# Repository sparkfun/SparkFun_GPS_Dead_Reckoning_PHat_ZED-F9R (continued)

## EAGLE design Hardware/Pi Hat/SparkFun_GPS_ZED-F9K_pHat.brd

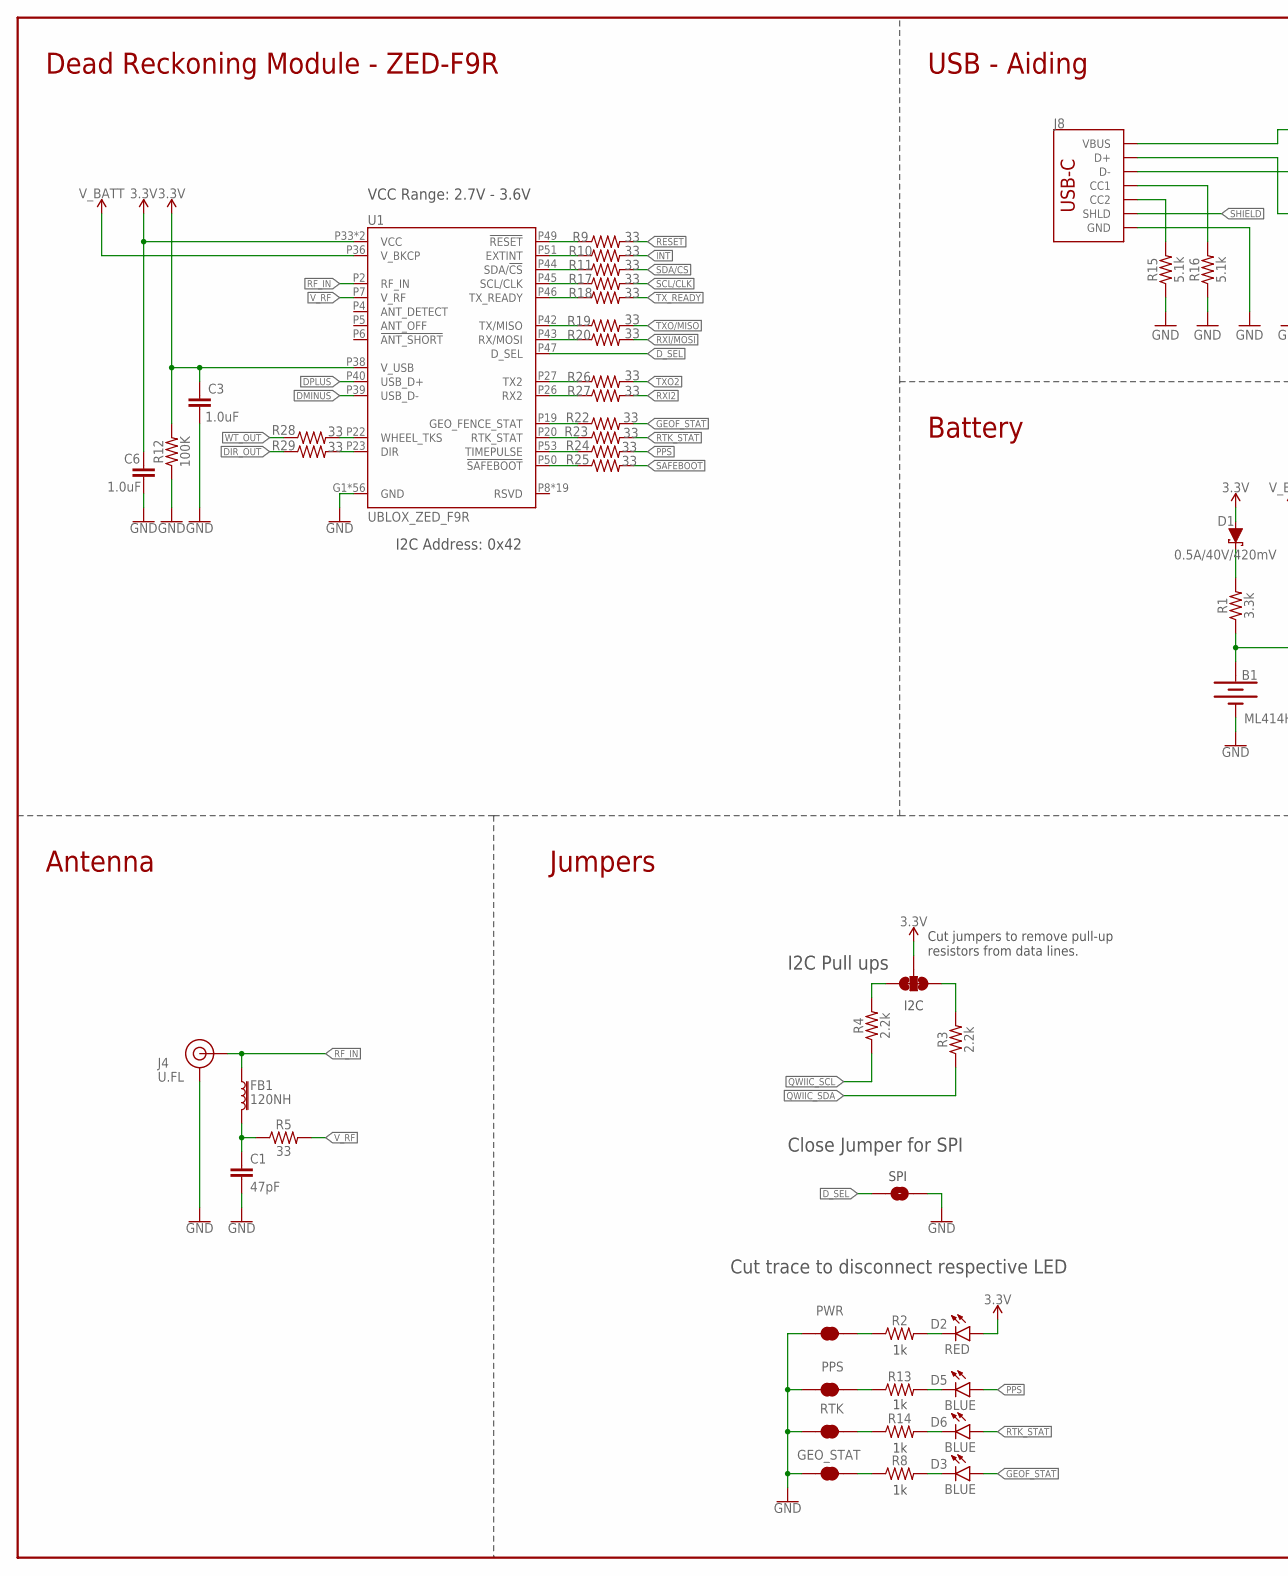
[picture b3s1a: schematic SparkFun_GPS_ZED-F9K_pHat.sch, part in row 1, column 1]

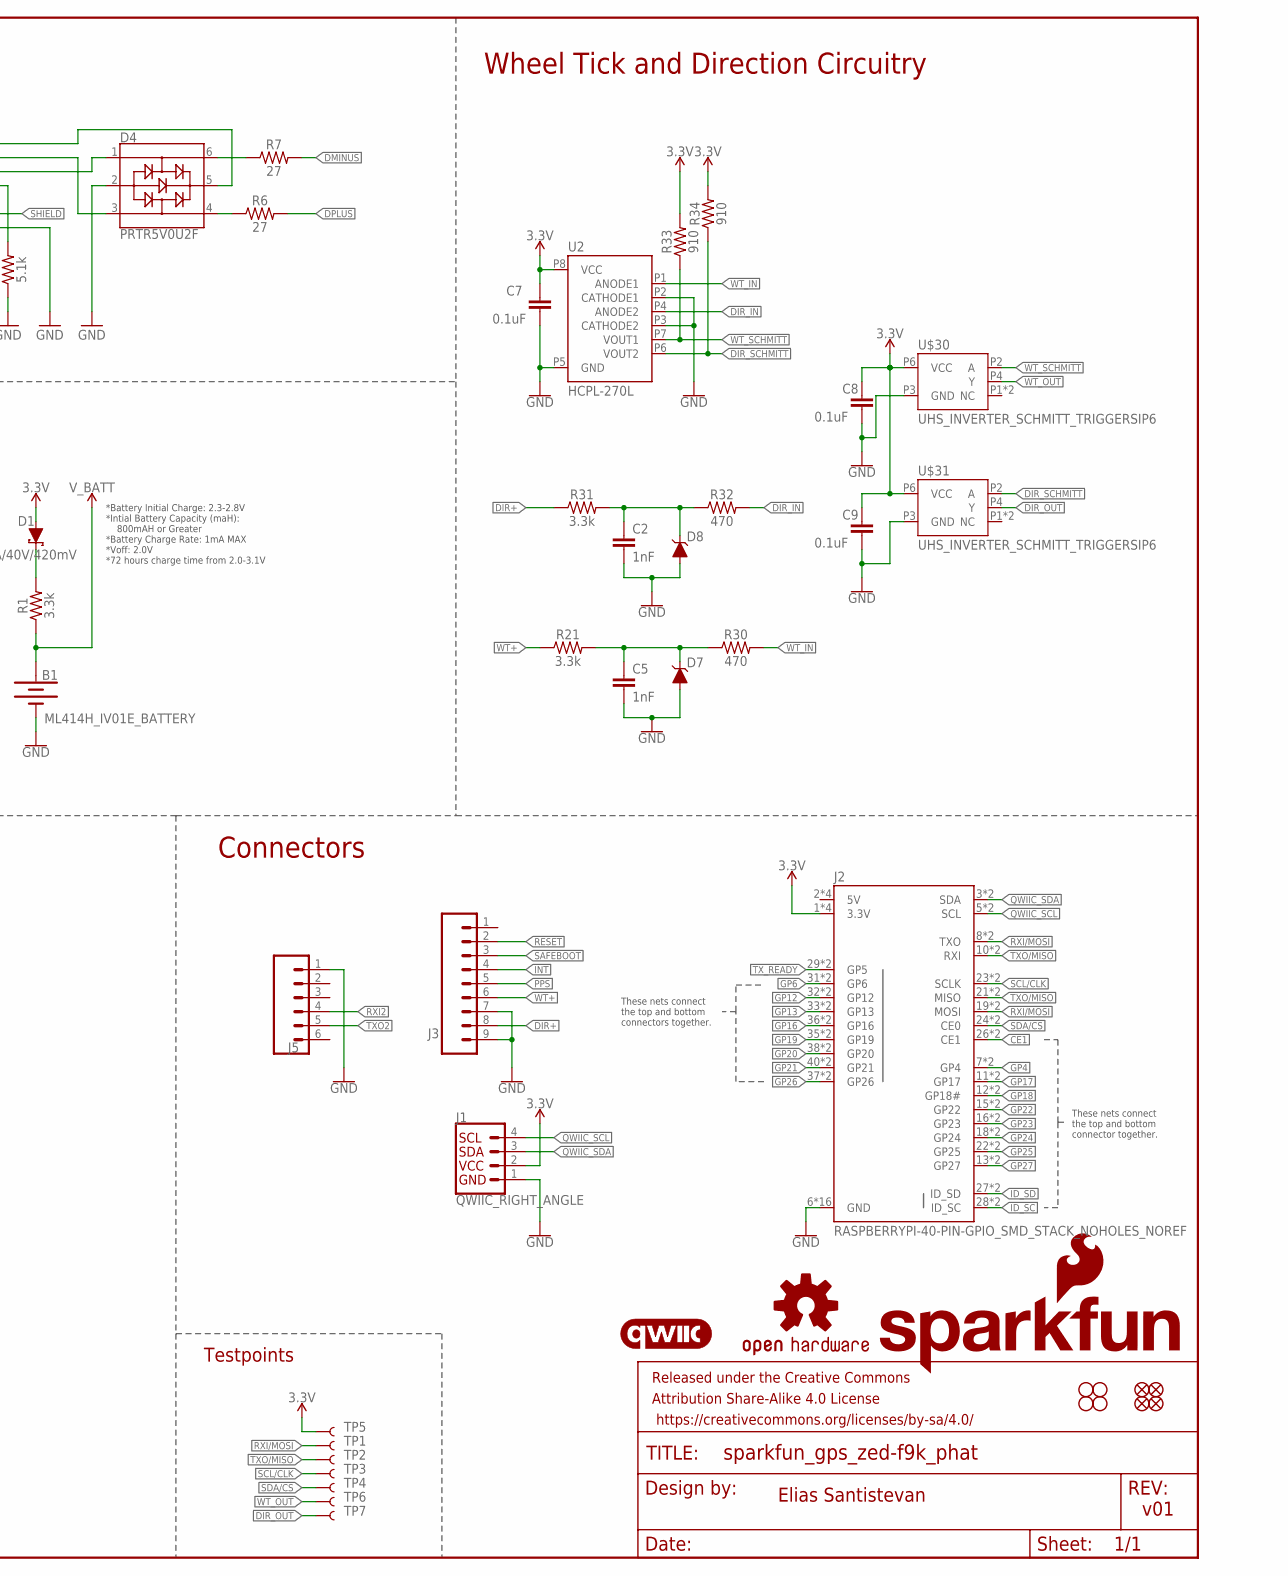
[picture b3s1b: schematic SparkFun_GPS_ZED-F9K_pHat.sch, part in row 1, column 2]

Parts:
B1: ML414H_IV01E_BATTERY; ML414H_IV01E
C1: 47pF; 0402
C2, C5: 1nF; 0402
C3, C6: 1.0uF; 0402
C7, C8, C9: 0.1uF; 0402
D1: 0.5A/40V/420mV; SOD-323
D2: RED; LED-0603
D3, D5, D6: BLUE; LED-0603
D4: PRTR5V0U2F; SOT886
D7, D8: 0.5A/40V/420mV; SOT23_BZX
FB1: 120NH; 0402_MURATA
FD9, FD10, FD11, FD12: FIDUCIALUFIDUCIAL; FIDUCIAL-MICRO
FRAME2: FRAME-LEDGER; CREATIVE_COMMONS
GEO_STAT: JUMPER-SMT_2_NC_TRACE_SILK; SMT-JUMPER_2_NC_TRACE_SILK
H9, H10, H11, H12: STAND-OFFTIGHT; STAND-OFF-TIGHT
J1: QWIIC_RIGHT_ANGLE; JST04_1MM_RA
J2: RASPBERRYPI-40-PIN-GPIO_SMD_STACK_NOHOLES_NOREF; RASPBERRY_PI_HAT_40_PIN_SMD_STACKABLE_NOHOLES_NOREF
J3: CONN_09NO_SILK; 1X09_NO_SILK
J4: U.FL
J5: CONN_06NO_SILK_NO_POP; 1X06_NO_SILK
J8: USB_C_2-LAYER; USB-C-16P
JP1: JUMPER-SMT_2_NO_SILK; SMT-JUMPER_2_NO_SILK
JP2: JUMPER-SMT_3_2-NC_TRACE_SILK; SMT-JUMPER_3_2-NC_TRACE_SILK
LOGO1: SFE_LOGO_NAME_FLAME.2_INCH; SFE_LOGO_NAME_FLAME_.2
LOGO2: OSHW-LOGOM; OSHW-LOGO-M
LOGO3: QWIIC_LOGO_5MM; QWIIC_5MM
PPS: JUMPER-SMT_2_NC_TRACE_SILK; SMT-JUMPER_2_NC_TRACE_SILK
PWR: JUMPER-SMT_2_NC_TRACE_SILK; SMT-JUMPER_2_NC_TRACE_SILK
R1, R21, R31: 3.3k; 0603
R2, R8, R13, R14: 1k; 0603
R3, R4: 2.2k; 0603
R5, R9, R10, R11, R17, R18, R19, R20, R22, R23, R24, R25, R26, R27, R28, R29: 33; 0603
R6, R7: 27; 0603
R12: 100K; 0402
R15, R16: 5.1k; 0402
R30, R32: 470; 0603
R33, R34: 910; 0603
RTK: JUMPER-SMT_2_NC_TRACE_SILK; SMT-JUMPER_2_NC_TRACE_SILK
TP1, TP2, TP3, TP4, TP5, TP6, TP7: TEST-POINT3X4; PAD.03X.04
U1: UBLOX_ZED_F9R
U2: HCPL-270L; SOP_8-PIN
U$30, U$31: UHS_INVERTER_SCHMITT_TRIGGERSIP6; SIP6

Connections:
3.3V: C3.1, C6.1, C7.1, C8.1, C9.1, D1.A, D2.A, J1.2, J2.1 (3.3V), J2.1B (3.3V), J2.17 (3.3V), J2.17B (3.3V), JP2.2, R12.2, R33.2, R34.2, TP5.P$1, U1.P33 (VCC), U1.P34 (VCC), U1.P38 (V_USB), U2.P8 (VCC), U$30.P6 (VCC), U$31.P6 (VCC)
5V: J2.2 (5V), J2.2B (5V), J2.4 (5V), J2.4B (5V)
!RESET: J3.2, R9.2
!SAFEBOOT: J3.3, R25.2
CE1: J2.26 (CE1), J2.26B (CE1)
DIR+: J3.8, R31.1
DIR_IN: R32.2, U2.P4 (ANODE2)
DIR_OUT: R29.1, TP7.P$1, U$31.P4 (Y)
DIR_SCHMITT: R34.1, U2.P6 (VOUT2), U$31.P2 (A)
DMINUS: R7.2, U1.P39 (USB_D-)
DPLUS: R6.2, U1.P40 (USB_D+)
D_SEL: JP1.1, U1.P47 (D_SEL)
GEOF_STAT: D3.A, R22.2
GND: B1.-, C1.2, C2.2, C3.2, C5.2, C6.2, C7.2, C8.2, C9.2, D4.2, D7.P1 (A), D8.P1 (A), GEO_STAT.1, J1.1, J2.6 (GND), J2.6B (GND), J2.9 (GND), J2.9B (GND), J2.14 (GND), J2.14B (GND), J2.20 (GND), J2.20B (GND), J2.25 (GND), J2.25B (GND), J2.30 (GND), J2.30B (GND), J2.34 (GND), J2.34B (GND), J2.39 (GND), J2.39B (GND), J3.7, J3.9, J4.1 (GND), J4.2 (GND), J5.1, J8.GND, J8.GND2 (GND), JP1.2, PPS.1, PWR.1, R12.1, R15.1, R16.1, RTK.1, U1.G1 (GND), U1.G2 (GND), U1.G3 (GND), U1.G4 (GND), U1.G5 (GND), U1.G6 (GND), U1.G7 (GND), U1.G8 (GND), U1.G9 (GND), U1.G10 (GND), U1.G11 (GND), U1.G12 (GND), U1.G13 (GND), U1.G14 (GND), U1.G15 (GND), U1.G16 (GND), U1.G17 (GND), U1.G18 (GND), U1.G19 (GND), U1.G20 (GND), U1.G21 (GND), U1.G22 (GND), U1.G23 (GND), U1.G24 (GND), U1.G25 (GND), U1.G26 (GND), U1.G27 (GND), U1.G28 (GND), U1.G29 (GND), U1.G30 (GND), U1.G31 (GND), U1.G32 (GND), U1.G33 (GND), U1.G34 (GND), U1.G35 (GND), U1.G36 (GND), U1.G37 (GND), U1.G38 (GND), U1.G39 (GND), U1.G40 (GND), U1.G41 (GND), U1.G42 (GND), U1.G43 (GND), U1.G44 (GND), U1.G45 (GND), U1.G46 (GND), U1.G47 (GND), U1.G48 (GND), U1.P1 (GND), U1.P3 (GND), U1.P12 (GND), U1.P14 (GND), U1.P32 (GND), U1.P37 (GND), U1.P41 (GND), U1.P48 (GND), U2.P2 (CATHODE1), U2.P3 (CATHODE2), U2.P5 (GND), U$30.P3 (GND), U$31.P3 (GND)
GP4: J2.7 (GP4), J2.7B (GP4)
GP6: J2.31 (GP6), J2.31B (GP6)
GP12: J2.32 (GP12), J2.32B (GP12)
GP13: J2.33 (GP13), J2.33B (GP13)
GP16: J2.36 (GP16), J2.36B (GP16)
GP17: J2.11 (GP17), J2.11B (GP17)
GP18: J2.12 (GP18#), J2.12B (GP18#)
GP19: J2.35 (GP19), J2.35B (GP19)
GP20: J2.38 (GP20), J2.38B (GP20)
GP21: J2.40 (GP21), J2.40B (GP21)
GP22: J2.15 (GP22), J2.15B (GP22)
GP23: J2.16 (GP23), J2.16B (GP23)
GP24: J2.18 (GP24), J2.18B (GP24)
GP25: J2.22 (GP25), J2.22B (GP25)
GP26: J2.37 (GP26), J2.37B (GP26)
GP27: J2.13 (GP27), J2.13B (GP27)
ID_SC: J2.28 (ID_SC), J2.28B (ID_SC)
ID_SD: J2.27 (ID_SD), J2.27B (ID_SD)
INT: J3.4, R10.2
unnamed: JP2.1, R3.2
unnamed: D1.C, R1.2
unnamed: JP2.3, R4.2
unnamed: D2.C, R2.2
unnamed: C1.1, FB1.P2 (2), R5.1
unnamed: D4.6, R7.1
unnamed: D4.4, R6.1
unnamed: PWR.2, R2.1
unnamed: D4.3, J8.A6 (D+), J8.B6 (D+)
unnamed: D4.5, J8.VBUS1 (VBUS), J8.VBUS2 (VBUS)
unnamed: D4.1, J8.A7 (D-), J8.B7 (D-)
unnamed: J8.B5 (CC2), R15.2
unnamed: R9.1, U1.P49 (!RESET!)
unnamed: R10.1, U1.P51 (EXTINT)
unnamed: R11.1, U1.P44 (SDA/!CS!)
unnamed: GEO_STAT.2, R8.1
unnamed: D3.C, R8.2
unnamed: J8.A5 (CC1), R16.2
unnamed: R17.1, U1.P45 (SCL/CLK)
unnamed: R18.1, U1.P46 (TX_READY)
unnamed: R19.1, U1.P42 (TX/MISO)
unnamed: R14.1, RTK.2
unnamed: PPS.2, R13.1
unnamed: D5.C, R13.2
unnamed: D6.C, R14.2
unnamed: R20.1, U1.P43 (RX/MOSI)
unnamed: C5.1, D7.P3 (C), R21.2, R30.1
unnamed: R22.1, U1.P19 (GEO_FENCE_STAT)
unnamed: R23.1, U1.P20 (RTK_STAT)
unnamed: R24.1, U1.P53 (TIMEPULSE)
unnamed: R25.1, U1.P50 (!SAFEBOOT!)
unnamed: R26.1, U1.P27 (TX2)
unnamed: R27.1, U1.P26 (RX2)
unnamed: R28.2, U1.P22 (WHEEL_TKS)
unnamed: R29.2, U1.P23 (DIR)
unnamed: C2.1, D8.P3 (C), R31.2, R32.1
PPS: D5.A, J3.5, R24.2
QWIIC_SCL: J1.4, J2.5 (SCL), J2.5B (SCL), R4.1
QWIIC_SDA: J1.3, J2.3 (SDA), J2.3B (SDA), R3.1
RF_IN: FB1.P1 (1), J4.FEED (SIGNAL), U1.P2 (RF_IN)
RTK_STAT: D6.A, R23.2
RXI2: J5.4, R27.2
RXI/MOSI: J2.8 (TXO), J2.8B (TXO), J2.19 (MOSI), J2.19B (MOSI), R20.2, TP1.P$1
SCL/CLK: J2.23 (SCLK), J2.23B (SCLK), R17.2, TP3.P$1
SDA/!CS: J2.24 (CE0), J2.24B (CE0), R11.2, TP4.P$1
SHIELD: J8.SHLD1 (SHLD), J8.SHLD2 (SHLD), J8.SHLD3 (SHLD), J8.SHLD4 (SHLD), J8.SHLD5 (SHLD), J8.SHLD6 (SHLD), J8.SHLD7 (SHLD), J8.SHLD8 (SHLD)
TXO2: J5.5, R26.2
TXO/MISO: J2.10 (RXI), J2.10B (RXI), J2.21 (MISO), J2.21B (MISO), R19.2, TP2.P$1
TX_READY: J2.29 (GP5), J2.29B (GP5), R18.2
V_BATT: B1.+, R1.1, U1.P36 (V_BKCP)
V_RF: R5.2, U1.P7 (V_RF)
WT+: J3.6, R21.1
WT_IN: R30.2, U2.P1 (ANODE1)
WT_OUT: R28.1, TP6.P$1, U$30.P4 (Y)
WT_SCHMITT: R33.1, U2.P7 (VOUT1), U$30.P2 (A)

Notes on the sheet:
v01
Elias Santistevan
Dead Reckoning Module - ZED-F9R
Battery
Connectors
Jumpers
Close Jumper for SPI
I2C Pull ups
Cut trace to disconnect respective LED
Antenna
*Battery Initial Charge: 2.3-2.8V *Intial Battery Capacity (maH): 800mAH or Greater *Battery Charge Rate: 1mA MAX *Voff: 2.0V *72 hours charge time from 2.0-3.1V
VCC Range: 2.7V - 3.6V
I2C Address: 0x42
USB - Aiding
Cut jumpers to remove pull-up resistors from data lines.
SPI
I2C
Testpoints
These nets connect the top and bottom connector together.
These nets connect the top and bottom connectors together.
Wheel Tick and Direction Circuitry

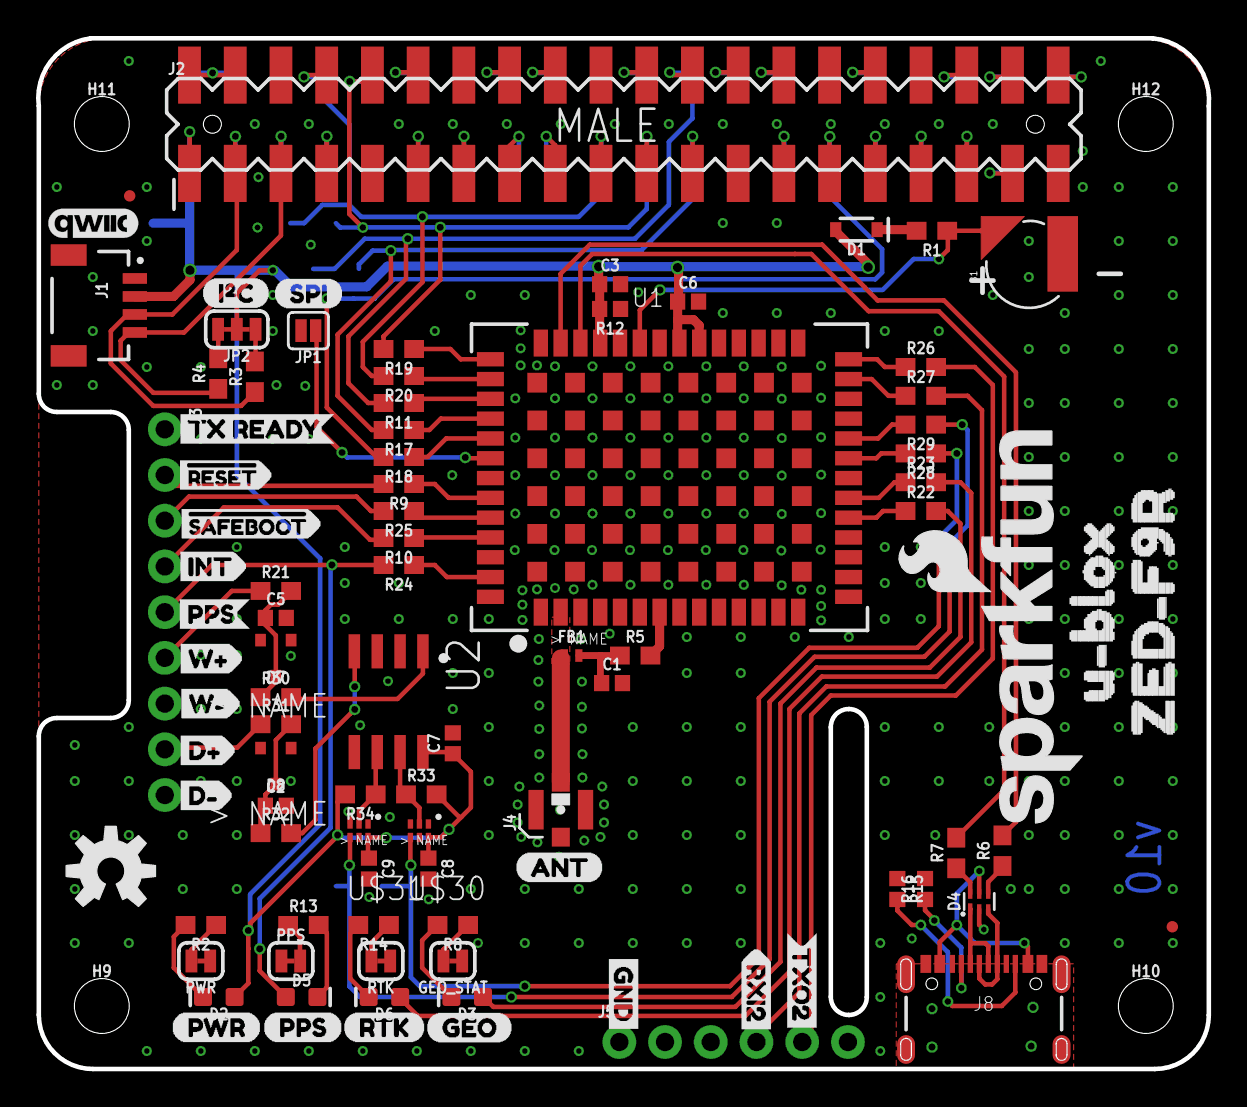
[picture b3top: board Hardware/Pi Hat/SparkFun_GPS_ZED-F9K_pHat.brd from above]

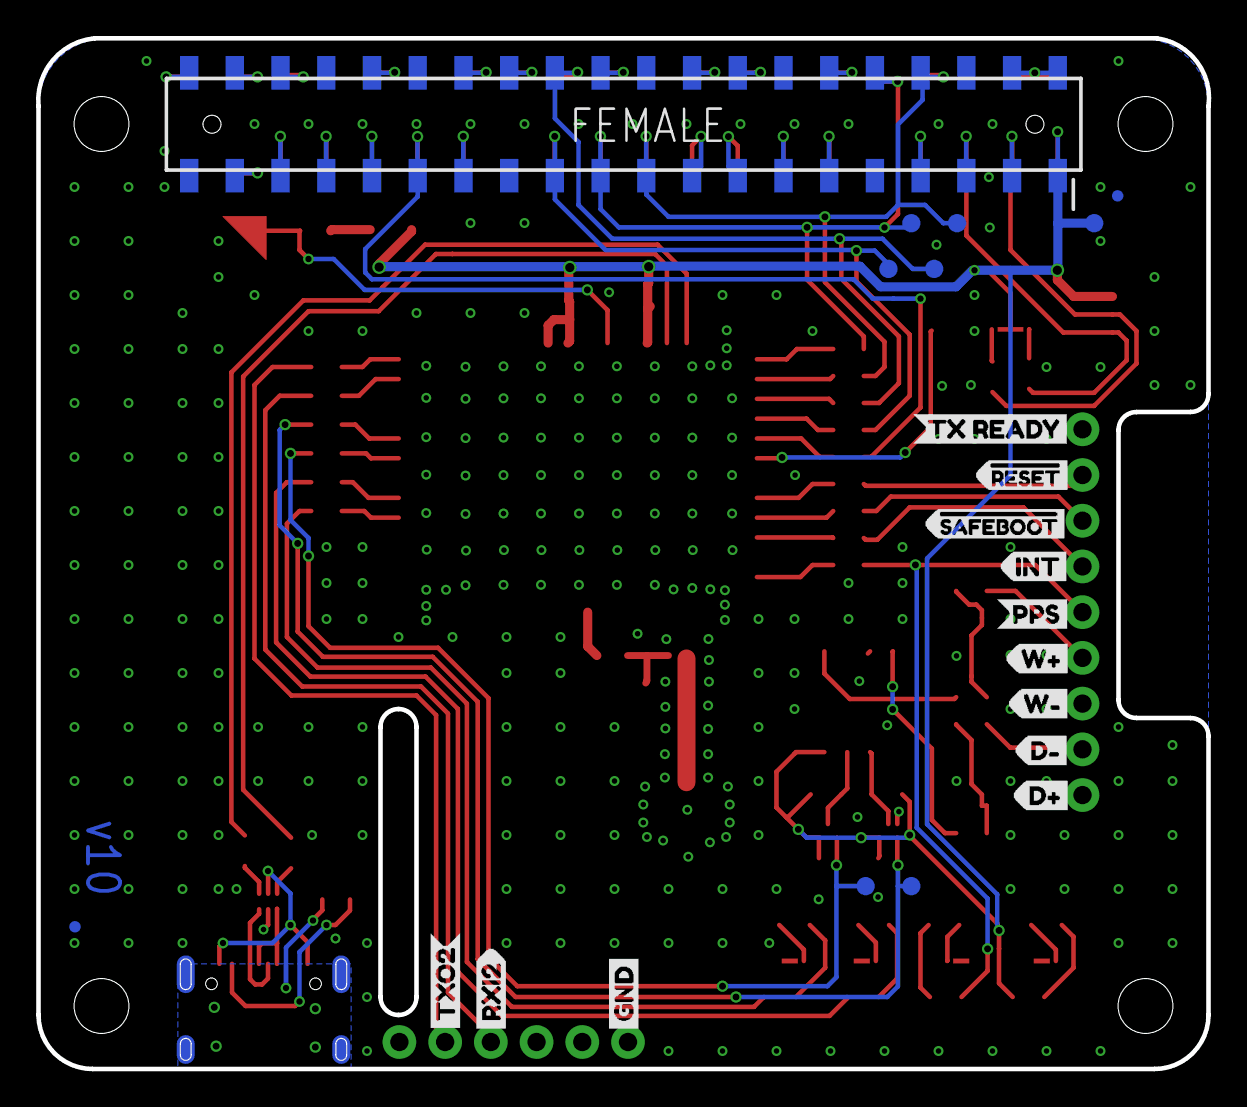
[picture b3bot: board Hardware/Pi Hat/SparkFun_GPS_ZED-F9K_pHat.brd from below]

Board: 2 copper layers, 65.0 x 57.3 mm, 120 parts (21 on the bottom side), 88 nets.

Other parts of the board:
U$1: INT1
U$2: PPS4
U$3: PPS6
U$4: PWR7
U$5: RTK5
U$6: RXI28
U$7: #RESET1
U$8: #RESET2
U$9, U$17: TX_READY0
U$10: TXO21
U$11: INT2
U$12: PPS1
U$13: #SAFEBOOT0
U$14: RXI26
U$15: #SAFEBOOT3
U$16: TXO25
U$18, U$19: GND-04
U$20: I_SUPER2_C-()-04
U$21: ANT1
U$22, U$32: D#0
U$23, U$33: D#1
U$24: SPI0
U$25: U#BLOX1
U$26: ZED#F9R0
U$27, U$34: W#2
U$28, U$35: W#3
U$29: GEO0

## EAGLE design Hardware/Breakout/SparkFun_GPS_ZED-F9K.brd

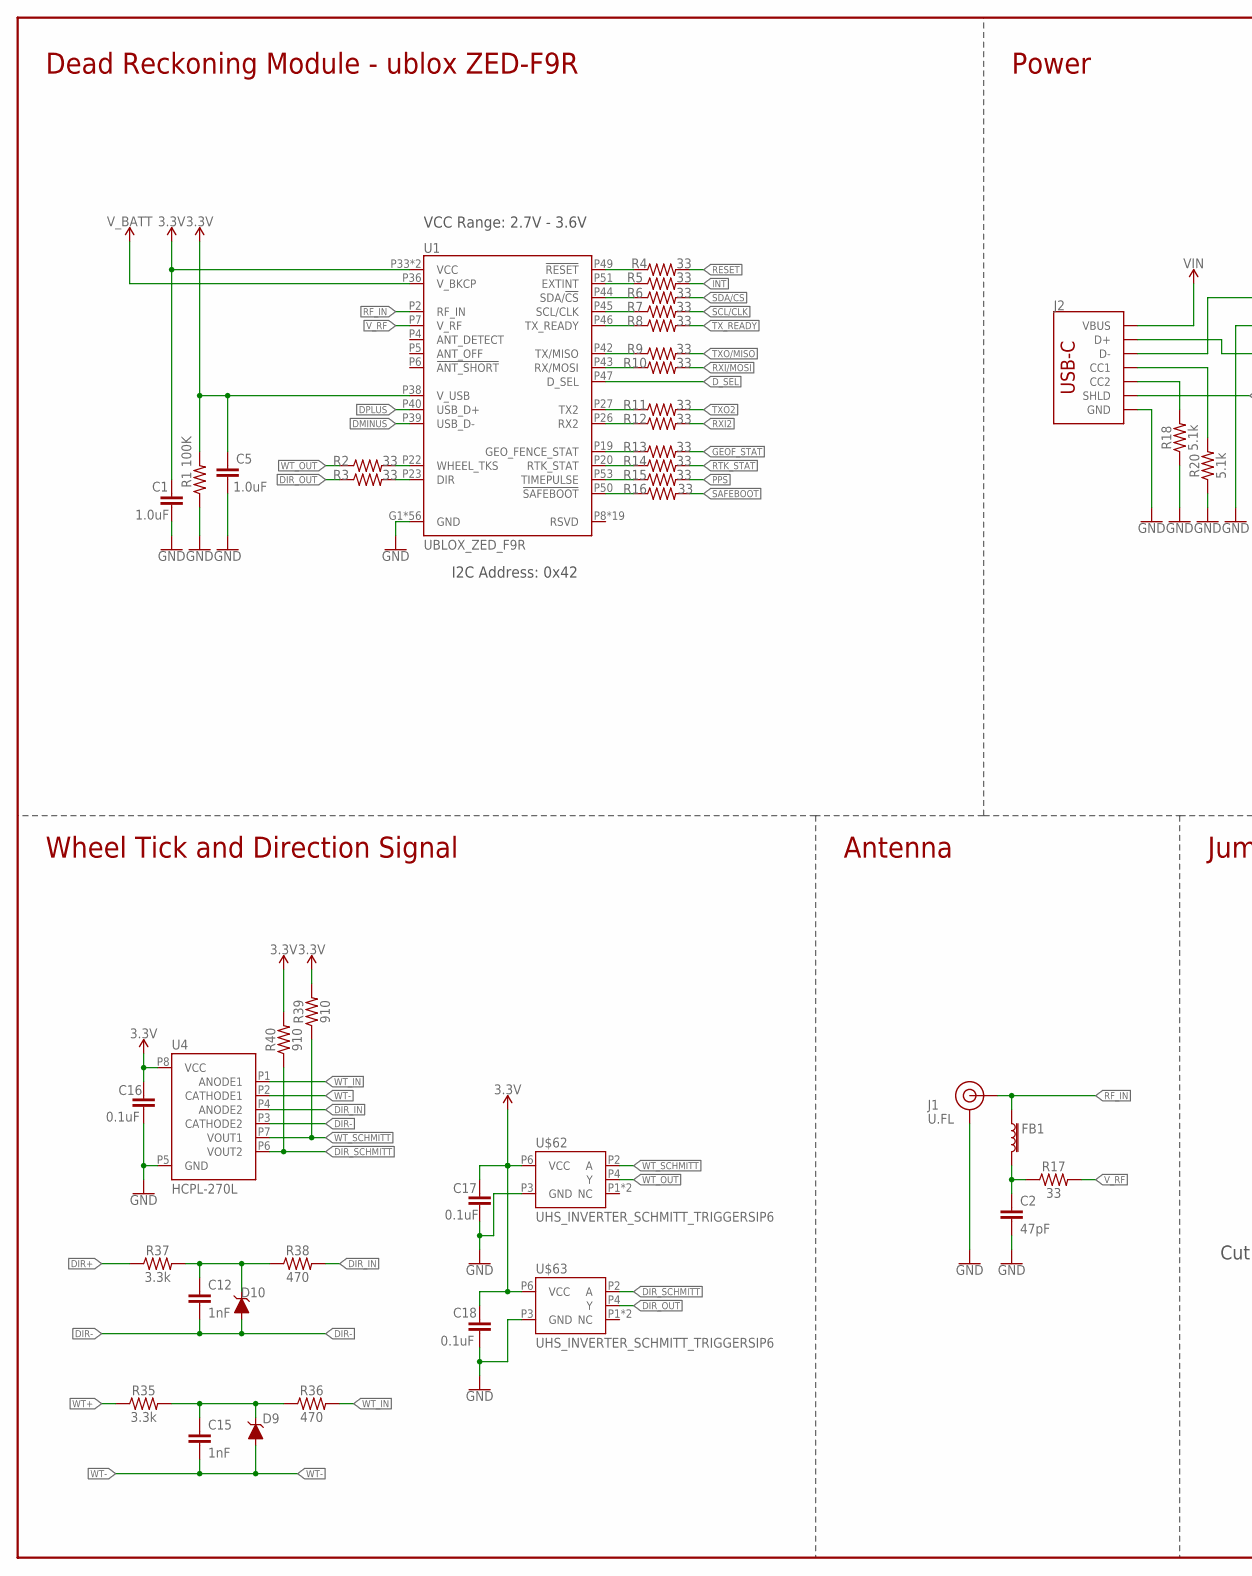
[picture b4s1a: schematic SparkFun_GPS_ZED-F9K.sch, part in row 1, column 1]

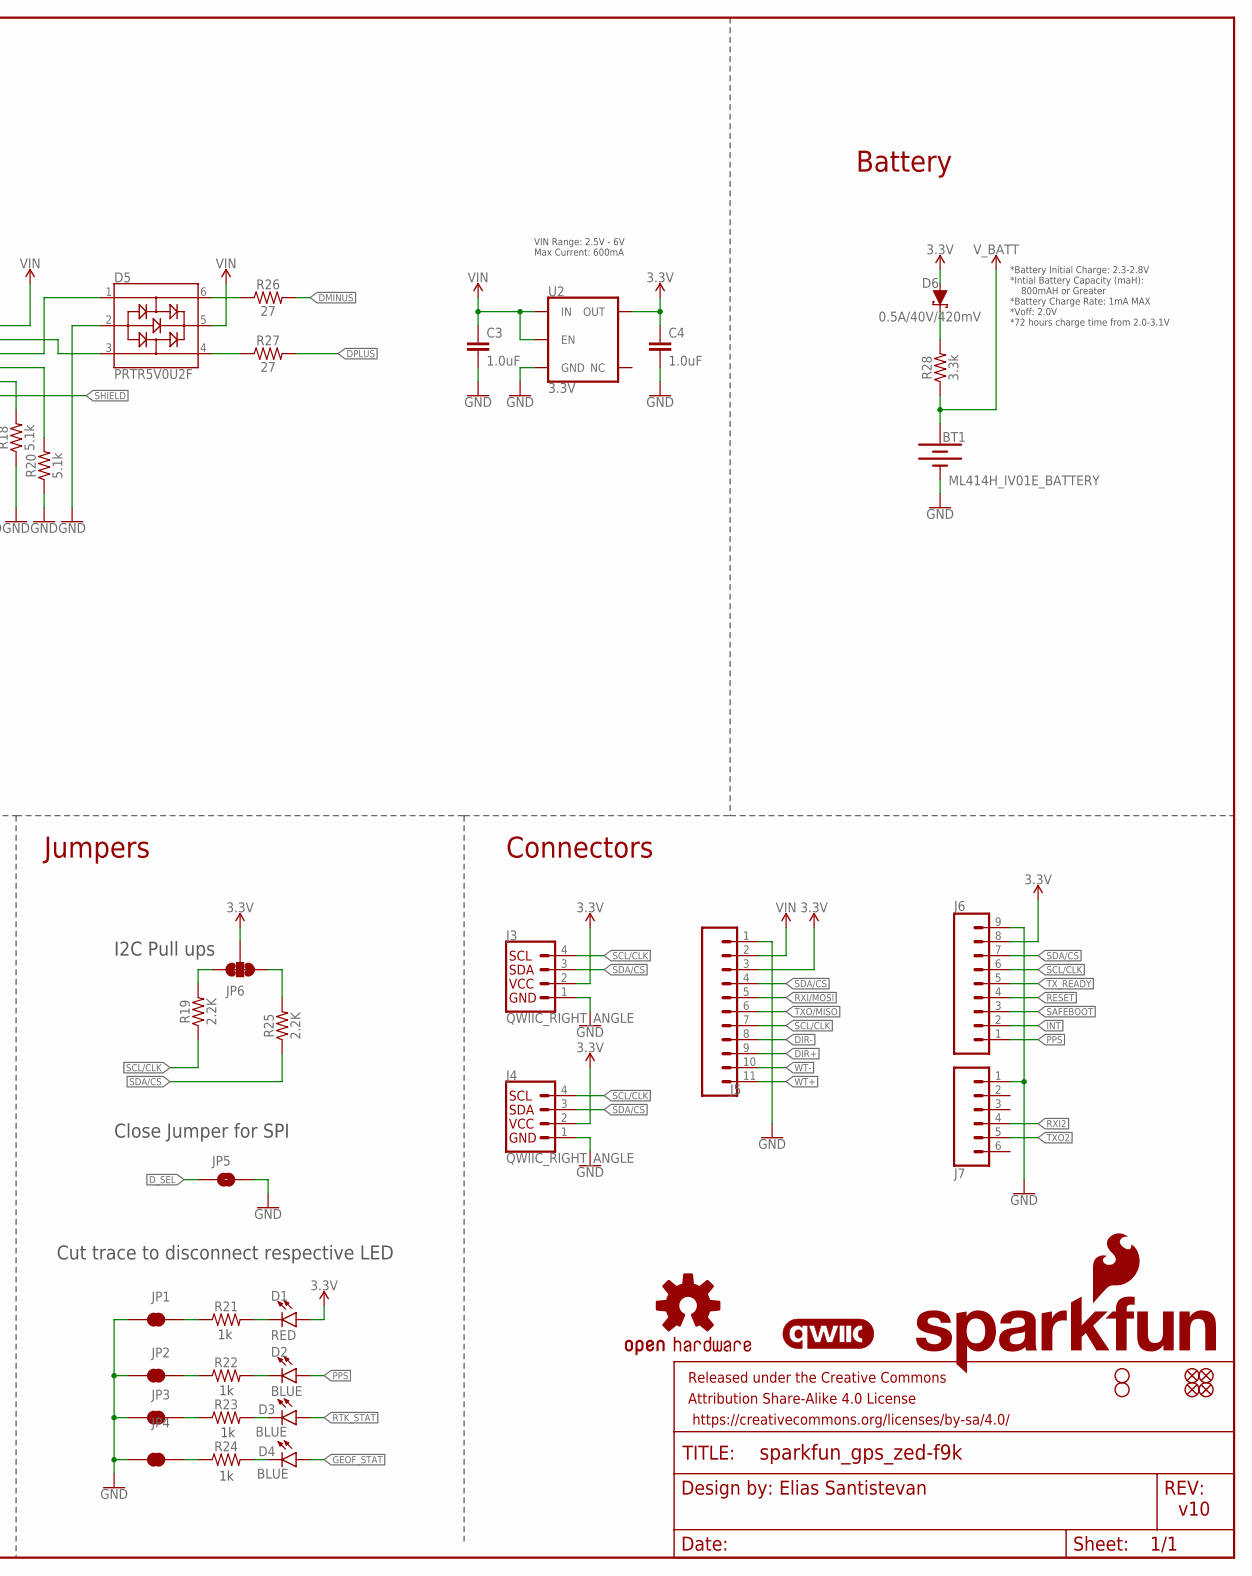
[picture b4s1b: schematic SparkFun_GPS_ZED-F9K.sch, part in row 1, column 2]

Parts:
$1_36_$_2020-02-13_17-32-45: STAND-OFFTIGHT; STAND-OFF-TIGHT
BT1: ML414H_IV01E_BATTERY; ML414H_IV01E
C1, C3, C4, C5: 1.0uF; 0603
C2: 47pF; 0402
C12, C15: 1nF; 0402
C16, C17, C18: 0.1uF; 0402
D1: RED; LED-0603
D2, D3, D4: BLUE; LED-0603
D5: PRTR5V0U2F; SOT886
D6: 0.5A/40V/420mV; SOD-323
D9, D10: 0.5A/40V/420mV; SOT23_BZX
FB1: 120NH; 0402_MURATA
FD1, FD2, FD3, FD4: FIDUCIALUFIDUCIAL; FIDUCIAL-MICRO
FRAME1: FRAME-LEDGER; CREATIVE_COMMONS
H2: STAND-OFFTIGHT; STAND-OFF-TIGHT
J1: U.FL
J2: USB_C_2-LAYER_PADS; USB-C-16P-2LAYER-PADS
J3, J4: QWIIC_RIGHT_ANGLE; JST04_1MM_RA
J5: CONN_111X11_NO_SILK; 1X11_NO_SILK
J6: CONN_09NO_SILK; 1X09_NO_SILK
J7: CONN_06NO_SILK_NO_POP; 1X06_NO_SILK
JP1, JP2, JP3, JP4: JUMPER-SMT_2_NC_TRACE_SILK; SMT-JUMPER_2_NC_TRACE_SILK
JP5: JUMPER-SMT_2_NO_SILK; SMT-JUMPER_2_NO_SILK
JP6: JUMPER-SMT_3_2-NC_TRACE_SILK; SMT-JUMPER_3_2-NC_TRACE_SILK
LOGO1: OSHW-LOGOM; OSHW-LOGO-M
LOGO2: QWIIC_LOGO_4MM; QWIIC_4MM
LOGO3: SFE_LOGO_NAME_FLAME.2_INCH; SFE_LOGO_NAME_FLAME_.2
R1: 100K; 0402
R2, R3, R4, R5, R6, R7, R8, R9, R10, R11, R12, R13, R14, R15, R16: 33; 0402
R17: 33; 0603
R18, R20: 5.1k; 0402
R19, R25: 2.2K; 0402
R21, R22, R23, R24: 1KOHM-0402-1/16W-1%; 0402
R26, R27: 27; 0603
R28, R35, R37: 3.3k; 0603
R36, R38: 470; 0603
R39, R40: 910; 0603
U1: UBLOX_ZED_F9R
U2: 3.3V; SOT23-5
U4: HCPL-270L; SOP_8-PIN
U$62, U$63: UHS_INVERTER_SCHMITT_TRIGGERSIP6; SIP6

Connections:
3.3V: C1.1, C4.1, C5.1, C16.1, C17.1, C18.1, D1.A, D6.A, J3.2, J4.2, J5.3, J6.8, JP6.2, R1.2, R39.2, R40.2, U1.P33 (VCC), U1.P34 (VCC), U1.P38 (V_USB), U2.5 (OUT), U4.P8 (VCC), U$62.P6 (VCC), U$63.P6 (VCC)
!RESET: J6.4, R4.2
!SAFEBOOT: J6.3, R16.2
DIR+: J5.9, R37.1
DIR-: C12.2, D10.P1 (A), J5.8, U4.P3 (CATHODE2)
DIR_IN: R38.2, U4.P4 (ANODE2)
DIR_OUT: R3.1, U$63.P4 (Y)
DIR_SCHMITT: R40.1, U4.P6 (VOUT2), U$63.P2 (A)
DMINUS: R26.2, U1.P39 (USB_D-)
DPLUS: R27.2, U1.P40 (USB_D+)
D_SEL: JP5.1, U1.P47 (D_SEL)
GEOF_STAT: D4.A, R13.2
GND: BT1.-, C1.2, C2.2, C3.2, C4.2, C5.2, C16.2, C17.2, C18.2, D5.2, J1.1 (GND), J1.2 (GND), J2.GND, J2.GND2 (GND), J3.1, J4.1, J5.1, J6.9, J7.1, JP1.1, JP2.1, JP3.1, JP4.1, JP5.2, R1.1, R18.1, R20.1, U1.G1 (GND), U1.G2 (GND), U1.G3 (GND), U1.G4 (GND), U1.G5 (GND), U1.G6 (GND), U1.G7 (GND), U1.G8 (GND), U1.G9 (GND), U1.G10 (GND), U1.G11 (GND), U1.G12 (GND), U1.G13 (GND), U1.G14 (GND), U1.G15 (GND), U1.G16 (GND), U1.G17 (GND), U1.G18 (GND), U1.G19 (GND), U1.G20 (GND), U1.G21 (GND), U1.G22 (GND), U1.G23 (GND), U1.G24 (GND), U1.G25 (GND), U1.G26 (GND), U1.G27 (GND), U1.G28 (GND), U1.G29 (GND), U1.G30 (GND), U1.G31 (GND), U1.G32 (GND), U1.G33 (GND), U1.G34 (GND), U1.G35 (GND), U1.G36 (GND), U1.G37 (GND), U1.G38 (GND), U1.G39 (GND), U1.G40 (GND), U1.G41 (GND), U1.G42 (GND), U1.G43 (GND), U1.G44 (GND), U1.G45 (GND), U1.G46 (GND), U1.G47 (GND), U1.G48 (GND), U1.P1 (GND), U1.P3 (GND), U1.P12 (GND), U1.P14 (GND), U1.P32 (GND), U1.P37 (GND), U1.P41 (GND), U1.P48 (GND), U2.2 (GND), U4.P5 (GND), U$62.P3 (GND), U$63.P3 (GND)
INT: J6.2, R5.2
unnamed: JP6.1, R25.2
unnamed: D6.C, R28.2
unnamed: JP6.3, R19.2
unnamed: D1.C, R21.2
unnamed: C2.1, FB1.P2 (2), R17.1
unnamed: D5.3, J2.A6 (D+), J2.B6 (D+)
unnamed: D5.1, J2.A7 (D-), J2.B7 (D-)
unnamed: JP1.2, R21.1
unnamed: D5.6, R26.1
unnamed: D5.4, R27.1
unnamed: R4.1, U1.P49 (!RESET!)
unnamed: R5.1, U1.P51 (EXTINT)
unnamed: J2.B5 (CC2), R18.2
unnamed: J2.A5 (CC1), R20.2
unnamed: R6.1, U1.P44 (SDA/!CS!)
unnamed: R7.1, U1.P45 (SCL/CLK)
unnamed: R8.1, U1.P46 (TX_READY)
unnamed: R9.1, U1.P42 (TX/MISO)
unnamed: R10.1, U1.P43 (RX/MOSI)
unnamed: R11.1, U1.P27 (TX2)
unnamed: JP3.2, R23.1
unnamed: JP2.2, R22.1
unnamed: D2.C, R22.2
unnamed: D3.C, R23.2
unnamed: R12.1, U1.P26 (RX2)
unnamed: R13.1, U1.P19 (GEO_FENCE_STAT)
unnamed: R14.1, U1.P20 (RTK_STAT)
unnamed: R15.1, U1.P53 (TIMEPULSE)
unnamed: R16.1, U1.P50 (!SAFEBOOT!)
unnamed: R2.2, U1.P22 (WHEEL_TKS)
unnamed: R3.2, U1.P23 (DIR)
unnamed: JP4.2, R24.1
unnamed: D4.C, R24.2
unnamed: C15.1, D9.P3 (C), R35.2, R36.1
unnamed: C12.1, D10.P3 (C), R37.2, R38.1
PPS: D2.A, J6.1, R15.2
RF_IN: FB1.P1 (1), J1.FEED (SIGNAL), U1.P2 (RF_IN)
RTK_STAT: D3.A, R14.2
RXI2: J7.4, R12.2
RXI/MOSI: J5.5, R10.2
SCL/CLK: J3.4, J4.4, J5.7, J6.6, R7.2, R19.1
SDA/!CS: J3.3, J4.3, J5.4, J6.7, R6.2, R25.1
SHIELD: J2.SHLD1 (SHLD), J2.SHLD2 (SHLD), J2.SHLD3 (SHLD), J2.SHLD4 (SHLD)
TXO2: J7.5, R11.2
TXO/MISO: J5.6, R9.2
TX_READY: J6.5, R8.2
VIN: C3.1, D5.5, J2.VBUS1 (VBUS), J2.VBUS2 (VBUS), J5.2, U2.1 (IN), U2.3 (EN)
V_BATT: BT1.+, R28.1, U1.P36 (V_BKCP)
V_RF: R17.2, U1.P7 (V_RF)
WT+: J5.11, R35.1
WT-: C15.2, D9.P1 (A), J5.10, U4.P2 (CATHODE1)
WT_IN: R36.2, U4.P1 (ANODE1)
WT_OUT: R2.1, U$62.P4 (Y)
WT_SCHMITT: R39.1, U4.P7 (VOUT1), U$62.P2 (A)

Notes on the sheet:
v10
Elias Santistevan
Dead Reckoning Module - ublox ZED-F9R
Battery
Connectors
Jumpers
Close Jumper for SPI
I2C Pull ups
Cut trace to disconnect respective LED
Antenna
*Battery Initial Charge: 2.3-2.8V *Intial Battery Capacity (maH): 800mAH or Greater *Battery Charge Rate: 1mA MAX *Voff: 2.0V *72 hours charge time from 2.0-3.1V
VIN Range: 2.5V - 6V Max Current: 600mA
Power
VCC Range: 2.7V - 3.6V
I2C Address: 0x42
Wheel Tick and Direction Signal

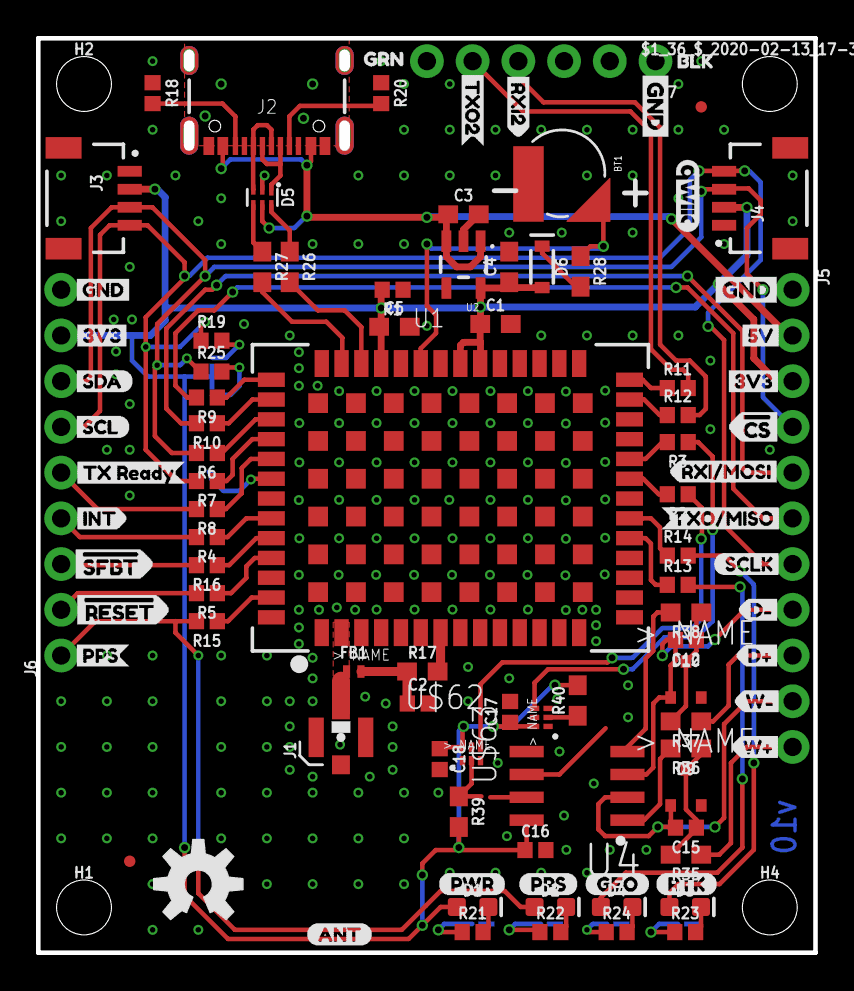
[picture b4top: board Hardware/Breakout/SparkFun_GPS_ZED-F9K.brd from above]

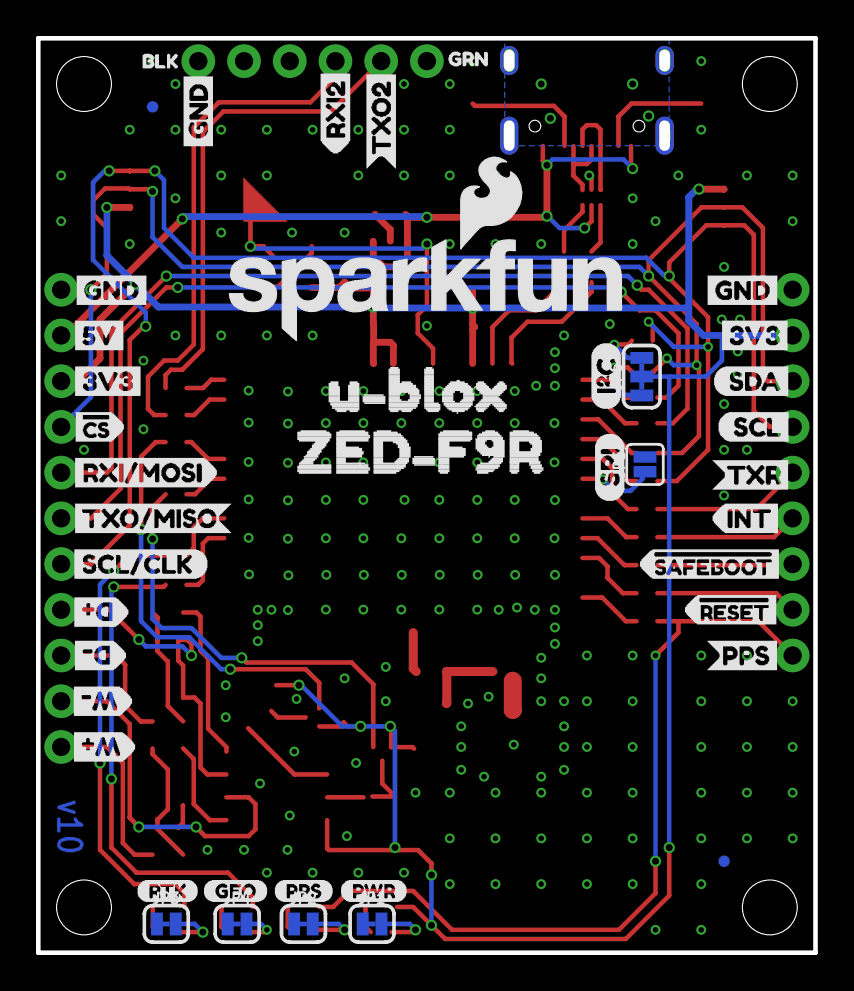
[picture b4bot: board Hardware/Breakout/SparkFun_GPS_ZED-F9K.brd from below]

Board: 2 copper layers, 43.2 x 50.8 mm, 147 parts (42 on the bottom side), 68 nets.

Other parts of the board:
H1, H4: STAND-OFFTIGHT; STAND-OFF-TIGHT
U$1, U$24: INT2
U$2: PPS4
U$3, U$19: 3V32
U$4, U$47: PPS8
U$5, U$48: PWR10
U$6: GND3
U$7: #RESET2
U$8, U$22: RTK9
U$9: RXI#MOSI5
U$10, U$60: D#0
U$11: SCL0
U$12: SDA1
U$13, U$61: D#1
U$14: RXI22
U$15: TXO#MISO6
U$16: TX_READY0
U$17, U$20: GND-03
U$18: 5V0
U$21, U$54: BLK2
U$23, U$53: GRN1
U$25, U$36: TXO21
U$26: CS#-<]-04
U$27: PPS1
U$28: #SAFEBOOT3
U$29, U$40: 3V3-04
U$30: RXI#MOSI0
U$31, U$34, U$41: GND-04
U$32, U$64: W#2
U$33: 5V
U$35: RXI28
U$37: TXO#MISO1
U$38: SCL#CLK2
U$39: SCL5
U$42: SDA4
U$43: TXR3
U$44: #RESET1
U$45: SPI4
U$46: I_SUPER2_C-()-04
U$49: ANT0
U$50, U$65: W#3
U$51: ZED#F9R0
U$52: U#BLOX1
U$55: #SFBT0
U$56, U$58: GEO1
U$57: SCLK2
U$59: CS#-[>-04
